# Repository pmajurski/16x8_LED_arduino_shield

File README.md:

# 16x8_LED_arduino_shield
16x8 LED display shield for Arduino Uno 

# Overview
This project is a custom shield for the Arduino Uno R3 and the controlling code. The display is two LuckyLight 8x8 LED matrices driven by two MAX7219 chips. Inputs for directional control, mode select, and brightness.
The display runs creatively named "display processes" which are relatively easy to create and add in. Display processes are broken up into animations and games. Animations can be static images, looping sequences of frames (ie gif), or animated sprites. Animations are non-interactive and ignore directional input. Games are interactive and use directional input.

# Controls
- Select toggles directional input between the current running process and mode select.
- Mode select: left / right cycles between animations, up / down cycles between games.
- Games are paused during mode select. Pressing select will unpause the active process. Animations ignore pause and will run during mode select.
- Brightness controls increase / decrease brightness. Default brightness can be adjusted in DisplayDriver.h

# Specs
- Display refresh and input polling at 50 Hz
- Powered by barrel jack connected to 9V battery. Optionally powered by Arduino Uno's barrel jack or USB.
- Display resolution of 16x8 pixels. Coordinate system is (y,x) with origin at top left corner. Y increases down, x increases right.
- Display draws roughly 340mA at full brightness.
 
# Creating new display processes
- Create a new child class of DisplayProcess
- Update animeProcesses or gameProcesses and their corresponding counts in .ino file.
- Display can be written to via a 16x8-bit frame buffer or 16x8-byte game matrix (which is then written to the frame buffer). 
- All processes share the frame buffer and game matrix.
- Sprites.cpp contains full frames stored in PROGMEM, which can be loaded directly into the frame buffer.

# Datasheets
- [MAX7219](https://www.sparkfun.com/datasheets/Components/General/COM-09622-MAX7219-MAX7221.pdf)
- [LuckyLight 8x8 LED matrix](https://cdn-shop.adafruit.com/datasheets/1820_KWM-R30881XPGB.pdf)

# Acknowledgements
- [forrestbao's kicad Arduino Uno shield footprint](https://github.com/forrestbao/arduino-kicad-library)
- [Adafruit Mini LED Gamer](https://github.com/adafruit/Adafruit_Learning_System_Guides/tree/master/Mini_LED_Gamer) - code for interrupt setup and modified snake game
- [MAX7219 driver wiring set up](https://playground.arduino.cc/Main/MAX72XXHardware/)

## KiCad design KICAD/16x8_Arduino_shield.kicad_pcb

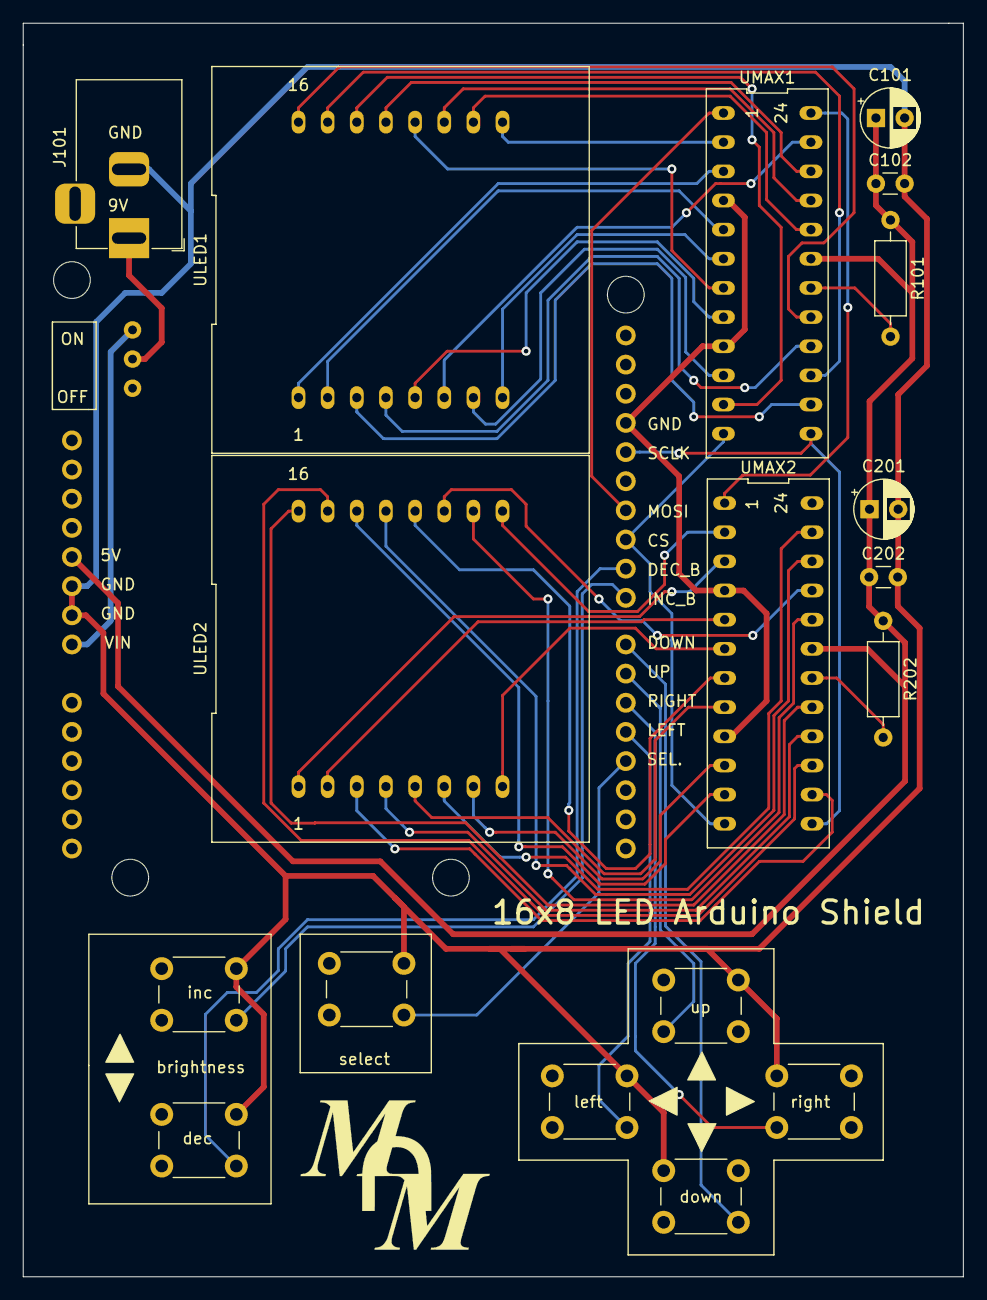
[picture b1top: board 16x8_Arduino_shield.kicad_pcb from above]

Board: 2 copper layers, 81.9 x 109.2 mm, 20 parts (0 on the bottom side), 49 nets.

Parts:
C101, C201: 10uF; CP_Radial_D5.0mm_P2.50mm
C102, C202: 100nF; C_Disc_D3.0mm_W1.6mm_P2.50mm
J101: Barrel_Jack; BarrelJack_Horizontal
R101, R202: 50K; R_Axial_DIN0207_L6.3mm_D2.5mm_P10.16mm_Horizontal
SW104: SW_SPDT; SPDT_switch_custom
ULED1, ULED2: 8x8_dot_matrix; LuckyLight_8x8_LED_matrix
UMAX1, UMAX2: MAX7219; MAX2719_custom
XA1: Arduino_Uno_Shield
dec: SW_Push; SW_PUSH_6mm
down: SW_Push; SW_PUSH_6mm
inc: SW_Push; SW_PUSH_6mm
left: SW_Push; SW_PUSH_6mm
right: SW_Push; SW_PUSH_6mm
select: SW_Push; SW_PUSH_6mm
up: SW_Push; SW_PUSH_6mm

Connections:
+5V: C101.1, C102.1, C201.1, C202.1, R101.1, R202.1, UMAX1.19, UMAX2.19, XA1.5V1
+9V: J101.1, SW104.2
/CS: UMAX1.12, UMAX2.12, XA1.D10
/MAX1_OUT: UMAX1.24, UMAX2.1
/MOSI: UMAX1.1, XA1.D11
/SCLK: UMAX1.13, UMAX2.13, XA1.D13
/VIN: SW104.1, XA1.VIN
/dec_bright: XA1.D9, dec.2
/down: XA1.D7, down.2
/inc_bright: XA1.D8, inc.2
/left: XA1.D4, left.2
/m1_col1: ULED1.13, UMAX1.22
/m1_col2: ULED1.3, UMAX1.14
/m1_col3: ULED1.4, UMAX1.16
/m1_col4: ULED1.10, UMAX1.20
/m1_col5: ULED1.6, UMAX1.23
/m1_col6: ULED1.11, UMAX1.21
/m1_col7: ULED1.15, UMAX1.15
/m1_col8: ULED1.16, UMAX1.17
/m1_row1: ULED1.9, UMAX1.2
/m1_row2: ULED1.14, UMAX1.11
/m1_row3: ULED1.8, UMAX1.6
/m1_row4: ULED1.12, UMAX1.7
/m1_row5: ULED1.1, UMAX1.3
/m1_row6: ULED1.7, UMAX1.10
/m1_row7: ULED1.2, UMAX1.5
/m1_row8: ULED1.5, UMAX1.8
/m2_col1: ULED2.13, UMAX2.22
/m2_col2: ULED2.3, UMAX2.14
/m2_col3: ULED2.4, UMAX2.16
/m2_col4: ULED2.10, UMAX2.20
/m2_col5: ULED2.6, UMAX2.23
/m2_col6: ULED2.11, UMAX2.21
/m2_col7: ULED2.15, UMAX2.15
/m2_col8: ULED2.16, UMAX2.17
/m2_row1: ULED2.9, UMAX2.2
/m2_row2: ULED2.14, UMAX2.11
/m2_row3: ULED2.8, UMAX2.6
/m2_row4: ULED2.12, UMAX2.7
/m2_row5: ULED2.1, UMAX2.3
/m2_row6: ULED2.7, UMAX2.10
/m2_row7: ULED2.2, UMAX2.5
/m2_row8: ULED2.5, UMAX2.8
/right: XA1.D5, right.2
/select: XA1.D3, select.2
/up: XA1.D6, up.2
GND: C101.2, C102.2, C201.2, C202.2, J101.2, UMAX1.4, UMAX1.9, UMAX2.4, UMAX2.9, XA1.GND1, XA1.GND2, XA1.GND3, dec.1, down.1, inc.1, left.1, right.1, select.1, up.1
unnamed: R101.2, UMAX1.18
unnamed: R202.2, UMAX2.18

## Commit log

2020-06-18 readme acknowledgements and datasheets
2020-06-18 code and pdfs from kicad
2020-06-18 ignore file
2020-06-18 ignore fix
2020-06-18 kicad files
2020-06-19 readme documenation
